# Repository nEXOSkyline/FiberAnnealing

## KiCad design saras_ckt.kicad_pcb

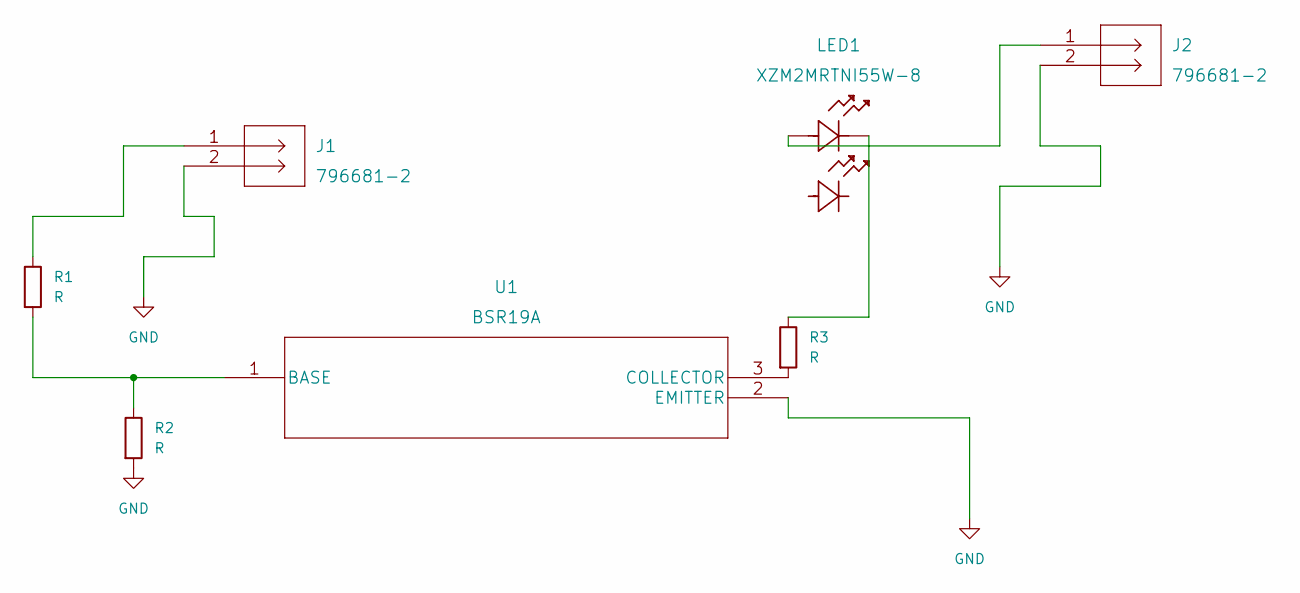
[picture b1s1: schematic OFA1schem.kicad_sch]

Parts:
J1, J2: 796681-2
LED1: XZM2MRTNI55W-8
R1, R2, R3: R; R_01005_0402Metric_Pad0.57x0.30mm_HandSolder
U1: BSR19A

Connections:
GND: J1.2, J2.2, R2.2, U1.2 (EMITTER)
unnamed: J1.1, R1.1
unnamed: J2.1, LED1.2
unnamed: LED1.1, R3.1
unnamed: R1.2, R2.1, U1.1 (BASE)
unnamed: R3.2, U1.3 (COLLECTOR)

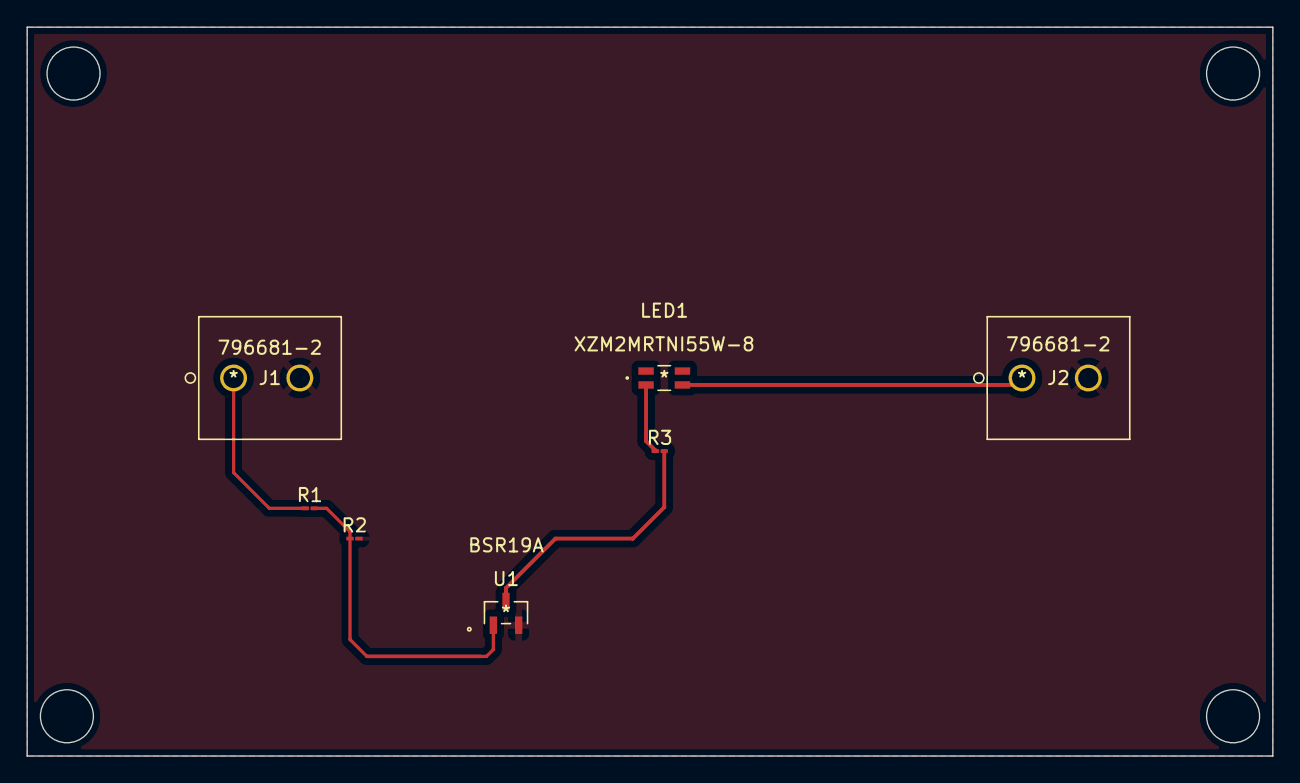
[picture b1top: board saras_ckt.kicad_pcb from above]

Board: 2 copper layers, 94.0 x 55.0 mm, 7 parts (0 on the bottom side), 6 nets.

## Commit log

2022-09-26 Add files via upload
    gerber and drill files

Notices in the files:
parts and their libraries:
Copyright 2021 Accelerated Designs. All rights reserved.
